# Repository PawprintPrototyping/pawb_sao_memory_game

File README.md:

# Paw SAO Memory Game

A [SAO](https://badge.team/docs/standards/sao/) shaped like a Paw that can play a memory game.  Opensource, originally designed for 
[Opensauce](https://opensauce.com) 2025 to encourage experimentation with microcontroller programming with the CH32V003F4P6.

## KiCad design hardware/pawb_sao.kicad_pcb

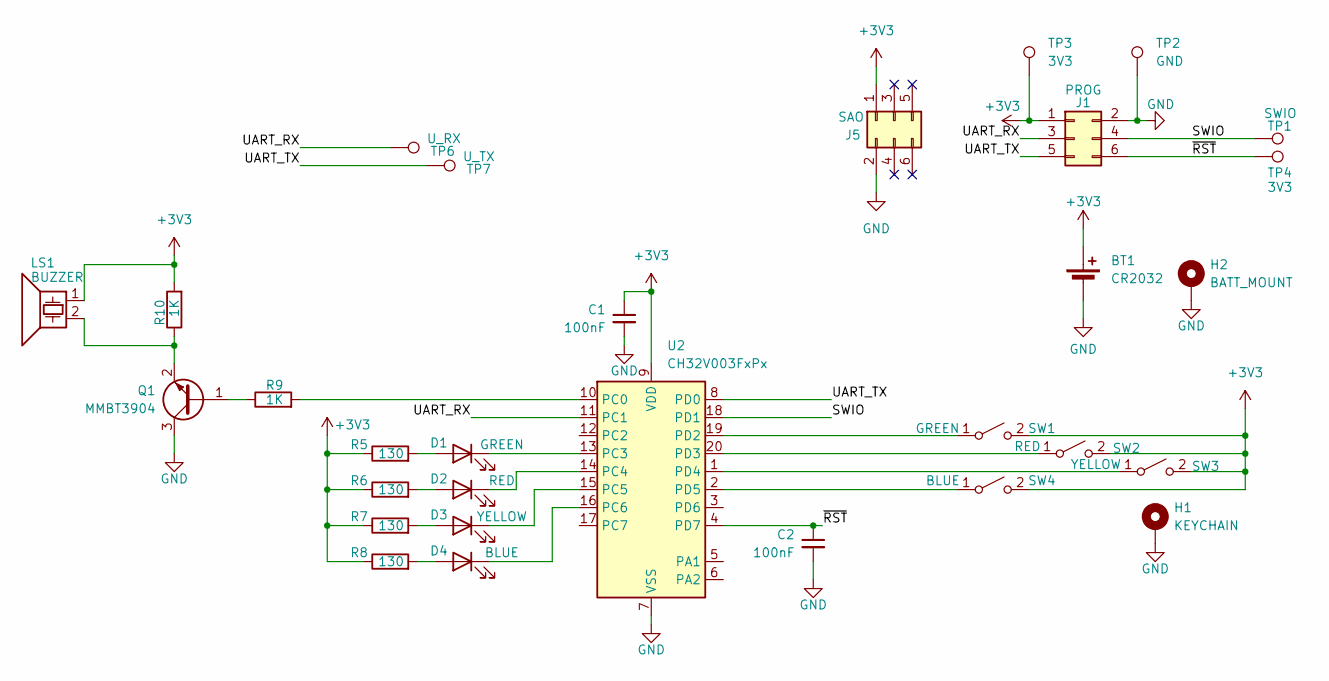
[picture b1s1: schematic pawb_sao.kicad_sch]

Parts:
BT1: CR2032; BH-25C-1_ADM_EZ
C1, C2: 100nF; C_0402_1005Metric
D1: GREEN; LED_0805_2012Metric
D2: RED; LED_0805_2012Metric
D3: YELLOW; LED_0805_2012Metric
D4: BLUE; LED_0805_2012Metric
H1: KEYCHAIN; MountingHole_3.2mm_M3_Pad_Via
H2: BATT_MOUNT; MountingHole_2.2mm_M2
J1: PROG; Paw-Connect_RevB_TC2030-IDC-NL_2x03_P1.27mm_Vertical
J5: SAO; PinHeader_2x03_P2.54mm_Vertical
LS1: BUZZER; FUET-9018
Q1: MMBT3904; SOT-23
R5, R6, R7, R8: 130; R_0603_1608Metric
R9, R10: 1K; R_0402_1005Metric
SW1: GREEN; SW_SPST_EVQP0
SW2: RED; SW_SPST_EVQP0
SW3: YELLOW; SW_SPST_EVQP0
SW4: BLUE; SW_SPST_EVQP0
TP1: SWIO; TestPoint_Pad_D1.5mm
TP2: GND; TestPoint_Pad_D1.5mm
TP3, TP4: 3V3; TestPoint_Pad_D1.5mm
TP6: U_RX; TestPoint_Pad_D1.5mm
TP7: U_TX; TestPoint_Pad_D1.5mm
U2: CH32V003FxPx; TSSOP-20_4.4x6.5mm_P0.65mm

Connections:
+3V3: BT1.1 (+), C1.1, J1.1, J5.1, LS1.1, R5.1, R6.1, R7.1, R8.1, R10.2, SW1.2 (B), SW2.2 (B), SW3.2 (B), SW4.2 (B), TP3.1, U2.9 (VDD)
/SWIO: J1.4, TP1.1, U2.18 (PD1)
/UART_RX: J1.3, TP6.1, U2.11 (PC1)
/UART_TX: J1.5, TP7.1, U2.8 (PD0)
/~RST: C2.1, J1.6, TP4.1, U2.4 (PD7)
GND: BT1.2 (-), C1.2, C2.2, H1.MP, H2.MP, J1.2, J5.2, Q1.3 (C), TP2.1, U2.7 (VSS)
unnamed: D1.2 (A), R5.2
unnamed: D1.1 (K), U2.13 (PC3)
unnamed: D2.2 (A), R6.2
unnamed: D2.1 (K), U2.14 (PC4)
unnamed: D3.2 (A), R7.2
unnamed: D3.1 (K), U2.15 (PC5)
unnamed: D4.2 (A), R8.2
unnamed: D4.1 (K), U2.16 (PC6)
unnamed: Q1.1 (B), R9.1
unnamed: LS1.2, Q1.2 (E), R10.1
unnamed: SW1.1 (A), U2.19 (PD2)
unnamed: SW2.1 (A), U2.20 (PD3)
unnamed: SW3.1 (A), U2.1 (PD4)
unnamed: SW4.1 (A), U2.2 (PD5)
unnamed: R9.2, U2.10 (PC0)

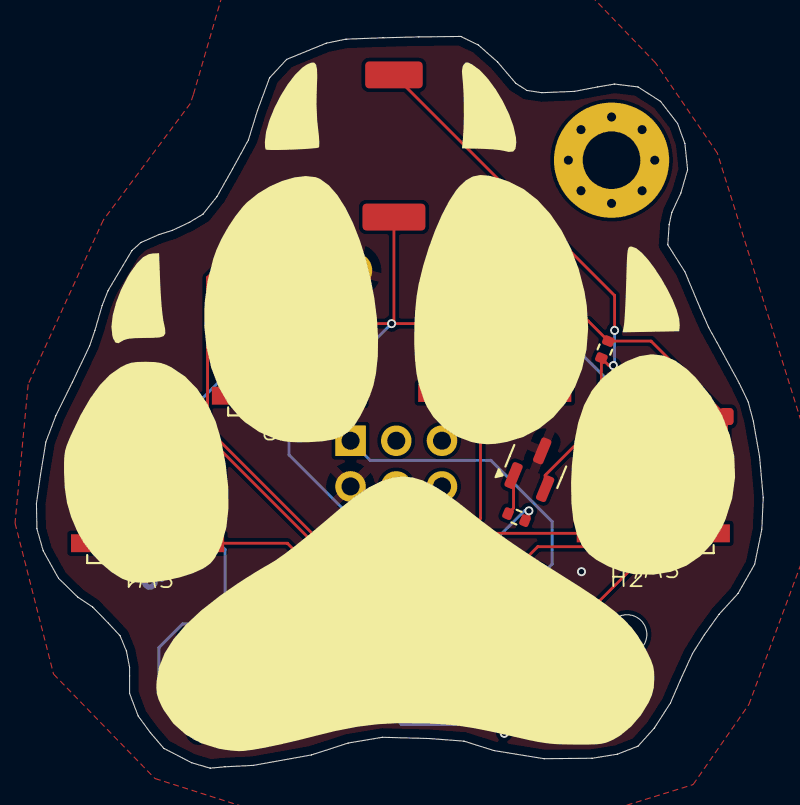
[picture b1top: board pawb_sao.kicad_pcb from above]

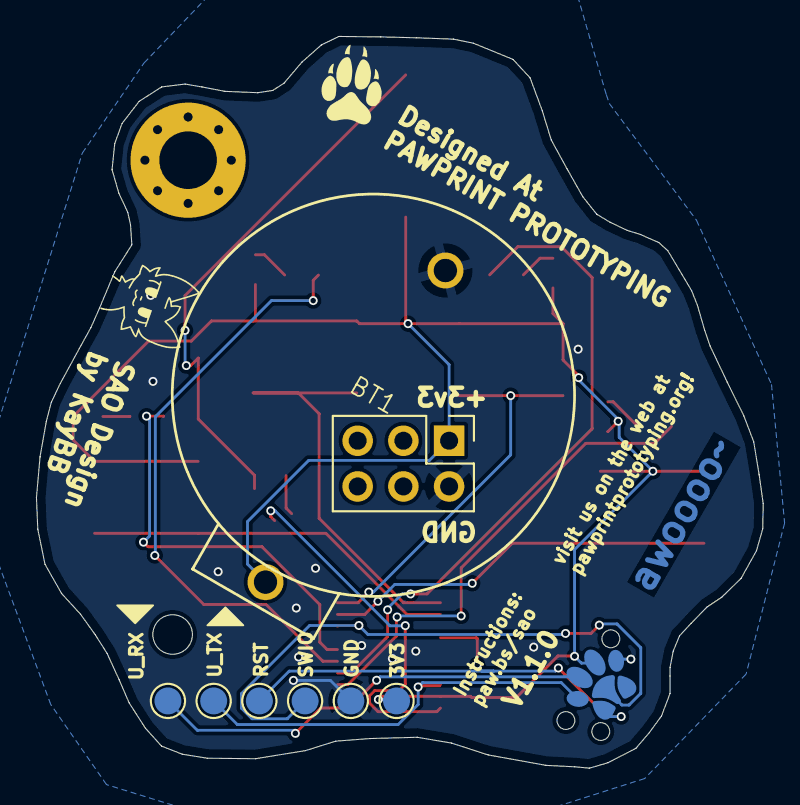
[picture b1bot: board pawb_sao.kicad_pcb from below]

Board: 2 copper layers, 40.4 x 40.6 mm, 30 parts (9 on the bottom side), 21 nets.

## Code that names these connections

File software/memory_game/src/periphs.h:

#ifndef _PERIPHS_H
#define _PERIPHS_H

#include "ch32fun.h"

#define NUM_COLORS  4

#define GREEN_LED   PC3
#define RED_LED     PC4
#define YELLOW_LED  PC5
#define BLUE_LED    PC6

#define GREEN_SW    PD2
#define RED_SW      PD3
#define YELLOW_SW   PD4
#define BLUE_SW     PD5

#define PIEZO_SPK   PC0

#define GREEN_NOTE	1908	
#define RED_NOTE	1515
#define YELLOW_NOTE	1276
#define BLUE_NOTE	956
#define LOSS_NOTE	5745

static uint8_t leds[] = {GREEN_LED, RED_LED, YELLOW_LED, BLUE_LED};
static uint8_t sws[] = {GREEN_SW, RED_SW, YELLOW_SW, BLUE_SW};

// Given a LED, return its switch
uint8_t led_to_sw(uint8_t led);

// Given a switch, return its LED
uint8_t sw_to_led(uint8_t sw);

// Beep for a given time
void beep(uint8_t sw, uint32_t time);

// Init all the GPIOs
void init_gpio();

// Set the state of an LED
void set_led(uint8_t led, uint8_t state);

// Set the state of all the LEDs at once
void set_all_leds(uint8_t state);

// Turn on an LED
void led_on(uint8_t led);

// Turn off an LED
void led_off(uint8_t led);

// Read a switch and beep. Might need to debounce this
uint8_t sw_read(uint8_t sw);

// Poll all the switches, return the switch that is pressed, 0 otherwise
uint8_t poll_switches();


#endif

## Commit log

2025-07-24 First
2025-07-24 untested deepsleep code
2025-08-01 made 3d model
